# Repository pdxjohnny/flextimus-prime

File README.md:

# Flextimus Prime

Posture monitor

## Getting Started

Make sure you have git configured.

```console
git config --global user.name 'Frist Last'
git config --global user.email 'first.last@example.com'
```

Install the git commit hooks. This will ensure that you can only commit if the
source compiles successfully.

> **WARNING** This adds `set auto-load safe-path /` to your `~/.gdbinit` which
> is not safe because when you start gdb it will now execute any commands in the
> `.gdbinit` file in the current directory.

```console
./scripts/install.sh
```

Find out what you should work on

```console
git todo
```

> This will be run every time you pull so that see todos added by others.

Create a new branch for your work

```console
git checkout -b describe_my_intended_changes
```

Now connect the board, and start `st-util`. From the the top level of this repo
run `arm-none-eabi-gdb` or `make gdb`.

Start hacking!

### Dependencies

1. [mbed](https://os.mbed.com/docs/v5.6/tools/setup.html)

## Contributing

See [CONTRIBUTING.md](https://github.com/pdxjohnny/flextimus-prime/blob/master/CONTRIBUTING.md)

## Team

- Max (lead)
- Julian
- John
- fouric

> Fall 2017
> Practicum Project

## Description

Your team will be responsible for designing, constructing, and demonstrating a small project as part of the course. The project is intended to both give you some necessary implementation skills and experience as well as serve as a model for your capstone experience. In fact, the capstone evaluation forms and worksheets will be used in evaluating and grading your practicum project.

You will get experience with PCB schematic and layout tools, project documentation and management tools, revision control systems, PCB assembly, and (depending upon your project) microcontroller IDEs.

Equally important, you will create project requirements, test plans, schedules, and documentation as you would for your capstone project (or a project in industry). Requirements Your project can do almost anything but must satisfy the following course requirements:

- Have one or more inputs or sensors
  - e.g. photodiodes, switches, accelerometers, pressure sensor, network data (wired or wireless), etc.

- Have one or more outputs or transducers
  - e.g. LEDs, LCDs, motors, networking (wired or wireless).

- Have one or more processing modules which control some of the outputs based on the inputs
  - e.g. analog filters, microcontrollers, FPGAs, etc.

- Use a two layer PCB that is between 1 and 16 in 2, with no side of the board being less than 1 inch or more than 12 inches.

- Use components that can be hand soldered or easily soldered in a crude reflow oven (no BGAs, uBGAs, LGAs, or components smaller than 0603 packages allowed)

## Grading Criteria

Your project will be evaluated using the capstone evaluation forms found on the capstone web site.

Portions of your practicum are evaluated separately throughout the course as part of the homework assignments.

Other aspects are evaluated as part of your project demonstration (final project presentation, design documentation, communication (e.g. weekly progress reports)). Originality Ideally, you should choose an original project idea or a new implementation of an existing idea. To receive an A on the practicum project you must not use existing work (unless specifically approved in advance by the instructor in writing).

If you choose to implement an existing design or incorporate existing work (including but not limited to schematics, layout, or code), your maximum achievable grade is a B.

However, you must disclose both what you've borrowed and the source.

Use of existing work that is not disclosed will result in a practicum grade of F. Recommendation It's far more important that your project be complete and functioning than complex. It's essential that you complete all aspects of the project from idea generation through requirements definition, design description/modeling, layout, construction, test, debug, and documentation.

It's important that you demonstrate a working project. A simple project designed and implemented completely by the team using the disciplined design process taught in class and demonstrably working will beat out an overly ambitious project that's incomplete, non-functioning, or haphazardly implemented.

Consider this in choosing a project. That's not to suggest you shouldn't be imaginative or ambitious. Everything else being equal, a creative points.

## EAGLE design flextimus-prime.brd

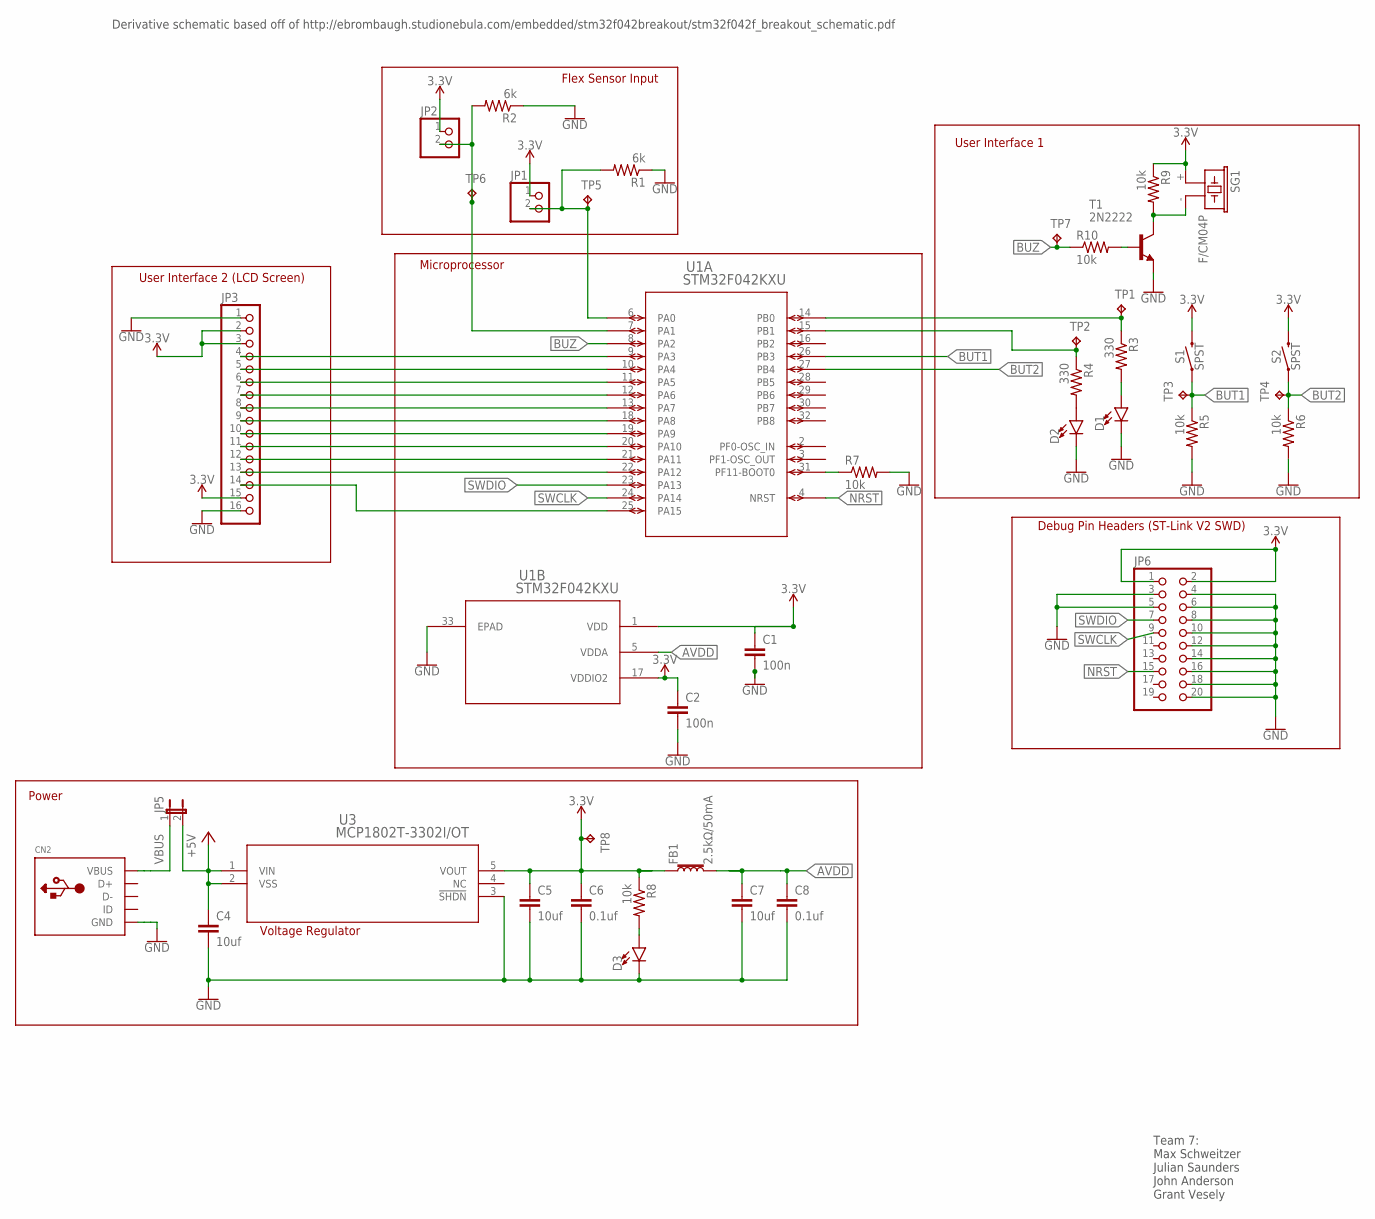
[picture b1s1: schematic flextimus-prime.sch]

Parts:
C1, C2: 100n; C0805
C4, C5, C7: 10uf; C0805
C6, C8: 0.1uf; C0805
CN2: USBMINIB; USB-MINIB
D1, D2, D3: LED10MM; LED_10MM
FB1: 2.5kΩ/50mA; 0603
JP1, JP2: PINHD-1X2; 1X02
JP3: PINHD-1X16; 1X16
JP5: JP1E; JP1
JP6: PINHD-2X10; 2X10
R1, R2: 6k; R0805
R3, R4: 330; R0805
R5, R6, R7, R8, R9, R10: 10k; R0805
S1, S2: SPST; TACTILE_SWITCH_PTH_6.0MM
SG1: F/CM04P
T1: 2N2222; TO92-EBC-OVAL
TP1, TP2, TP3, TP4, TP5, TP6, TP7, TP8: TPB2,54; B2,54
U1: STM32F042KXU; UFQFPN32-5X5MM
U3: MCP1802T-3302I/OT; SOT-23-5_MC

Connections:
3.3V: C1.1, C2.1, C5.1, C6.1, FB1.1, JP1.1, JP2.1, JP3.2, JP3.3, JP3.15, JP6.1, JP6.2, R8.1, R9.1, S1.3 (2), S2.3 (2), SG1.+ (1), TP8.TP, U1.1 (VDD), U1.17 (VDDIO2), U3.5 (VOUT)
+5V: C4.1, JP5.2, U3.1 (VIN), U3.2 (VSS)
AVDD: C7.1, C8.1, FB1.2, U1.5 (VDDA)
BUT1: R5.1, S1.1, TP3.TP, U1.26 (PB3)
BUT2: R6.1, S2.1, TP4.TP, U1.27 (PB4)
BUZ: R10.1, TP7.TP, U1.8 (PA2)
GND: C1.2, C2.2, C4.2, C5.2, C6.2, C7.2, C8.2, CN2.GND, D1.C, D2.C, D3.C, JP3.1, JP3.16, JP6.3, JP6.4, JP6.5, JP6.6, JP6.8, JP6.10, JP6.12, JP6.14, JP6.16, JP6.18, JP6.20, R1.1, R2.1, R5.2, R6.2, R7.2, T1.E, U1.33 (EPAD), U3.3 (!SHDN)
unnamed: JP1.2, R1.2, TP5.TP, U1.6 (PA0)
unnamed: JP2.2, R2.2, TP6.TP, U1.7 (PA1)
unnamed: R3.1, TP1.TP, U1.14 (PB0)
unnamed: JP3.14, U1.25 (PA15)
unnamed: D1.A, R3.2
unnamed: D2.A, R4.2
unnamed: R9.2, SG1.- (2), T1.C
unnamed: R10.2, T1.B
unnamed: D3.A, R8.2
unnamed: JP3.4, U1.9 (PA3)
unnamed: JP3.5, U1.10 (PA4)
unnamed: JP3.6, U1.11 (PA5)
unnamed: JP3.7, U1.12 (PA6)
unnamed: JP3.8, U1.13 (PA7)
unnamed: JP3.9, U1.18 (PA8)
unnamed: JP3.10, U1.19 (PA9)
unnamed: JP3.11, U1.20 (PA10)
unnamed: JP3.12, U1.21 (PA11)
unnamed: JP3.13, U1.22 (PA12)
unnamed: R7.1, U1.31 (PF11-BOOT0)
unnamed: R4.1, TP2.TP, U1.15 (PB1)
NRST: JP6.15, U1.4 (NRST)
SWCLK: JP6.9, U1.24 (PA14)
SWDIO: JP6.7, U1.23 (PA13)
VBUS: CN2.VBUS, JP5.1

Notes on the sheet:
Derivative schematic based off of http://ebrombaugh.studionebula.com/embedded/stm32f042breakout/stm32f042f_breakout_schematic.pdf
Power
User Interface 1
Debug Pin Headers (ST-Link V2 SWD)
Voltage Regulator
Flex Sensor Input
User Interface 2 (LCD Screen)
Microprocessor
Team 7: Max Schweitzer Julian Saunders John Anderson Grant Vesely

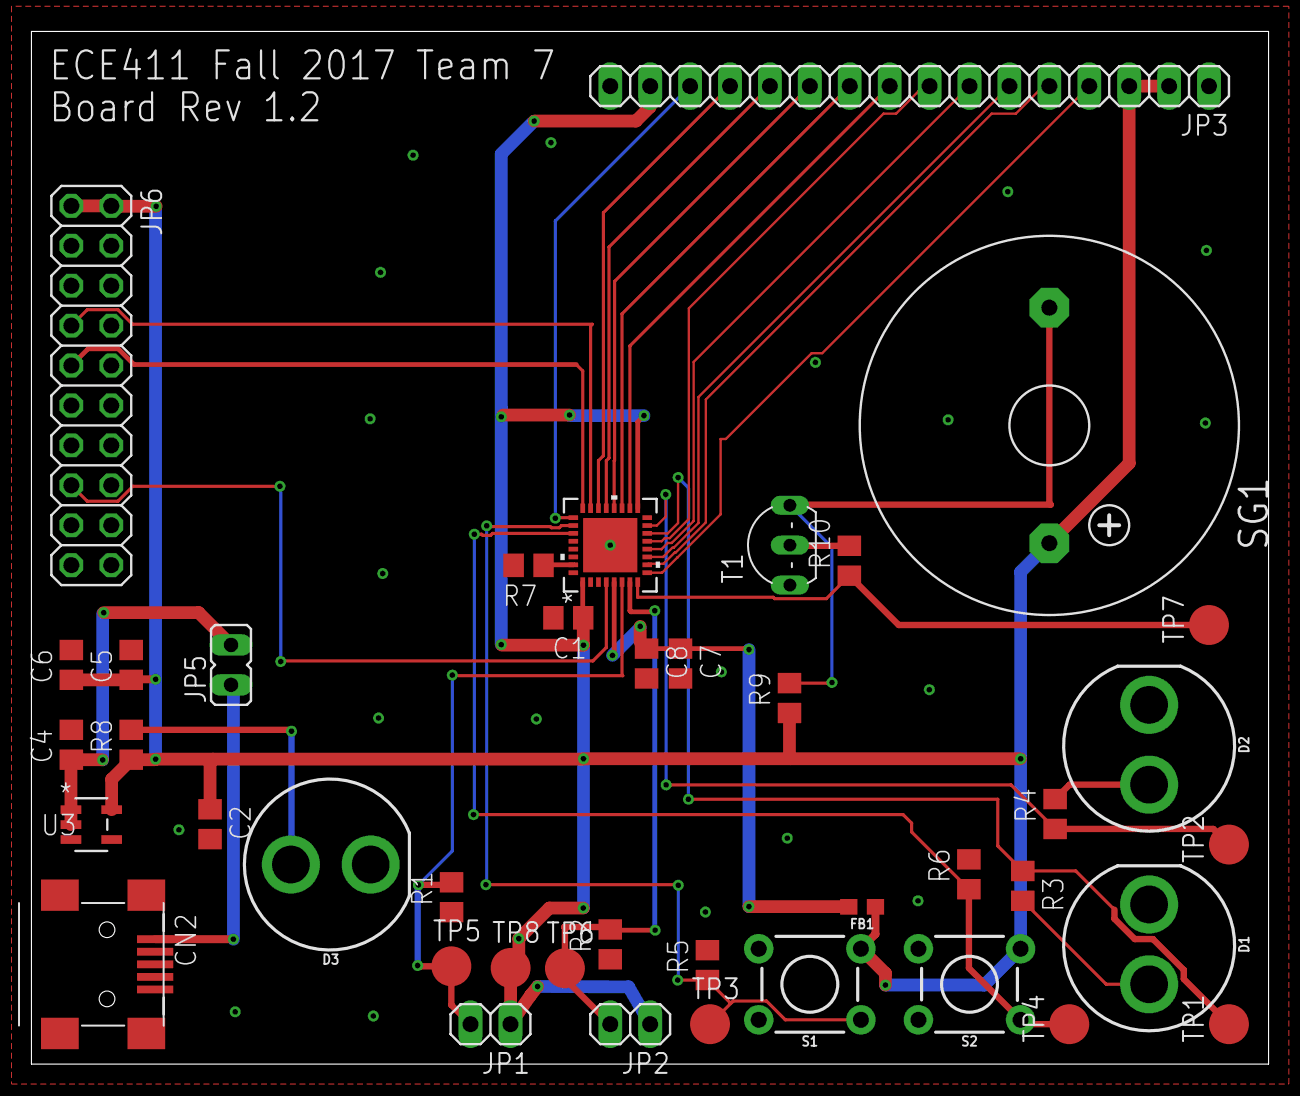
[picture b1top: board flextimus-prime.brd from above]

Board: 2 copper layers, 78.7 x 65.7 mm, 41 parts (0 on the bottom side), 32 nets.

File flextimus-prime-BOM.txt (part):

Partlist exported from C:/Users/Crimson/AppData/Local/Temp/Rar$DIa0.229/flextimus-prime.sch at 11/30/2017 9:41 PM

Part Value             Device                          Package                  Description                                       COPYRIGHT                                                 MANUFACTURER_PART_NUMBER MF MPN OC_FARNELL OC_NEWARK PROD_ID     SF_SKU    TP_SIGNAL_NAME VALUE    VENDOR            
C1   100n              C-EUC0805                       C0805                    CAPACITOR, European symbol                                                                                                                                                                                                       
C2   100n              C-EUC0805                       C0805                    CAPACITOR, European symbol                                                                                                                                                                                                       
C4   10uf              C-EUC0805                       C0805                    CAPACITOR, European symbol                                                                                                                                                                                                       
C5   10uf              C-EUC0805                       C0805                    CAPACITOR, European symbol                                                                                                                                                                                                       
C6   0.1uf             C-EUC0805                       C0805                    CAPACITOR, European symbol                                                                                                                                                                                                       
C7   10uf              C-EUC0805                       C0805                    CAPACITOR, European symbol                                                                                                                                                                                                       
C8   0.1uf             C-EUC0805                       C0805                    CAPACITOR, European symbol                                                                                                                                                                                                       
CN2                    USBMINIB                        USB-MINIB                USB Connectors                                                                                                                                                                                                                   
D1                     LED10MM                         LED_10MM                 LED (Generic)                                                                                                                                                                                                                    
D2                     LED10MM                         LED_10MM                 LED (Generic)                                                                                                                                                                                                                    
D3                     LED10MM                         LED_10MM                 LED (Generic)                                                                                                                                                                                                                    
FB1  2.5kO/50mA        FERRITE_BEAD-0603               0603                     Ferrite Bead (blocks, cores, rings, chokes, etc.)                                                                                                                NDUC-07859                           30O/1.8A                   
JP1                    PINHD-1X2                       1X02                     PIN HEADER                                                                                                                                                                                                                       
JP2                    PINHD-1X2                       1X02                     PIN HEADER                                                                                                                                                                                                                       
JP3                    PINHD-1X16                      1X16                     PIN HEADER                                                                                                                                                                                                                       
JP5                    JP1E                            JP1                      JUMPER                                                                                                                                                                                                                           
JP6                    PINHD-2X10                      2X10                     PIN HEADER                                                                                                                                                                                                                       
R1   6k                R-US_R0805                      R0805                    RESISTOR, American symbol                                                                                                                                                                                                        
R2   6k                R-US_R0805                      R0805                    RESISTOR, American symbol                                                                                                                                                                                                        
R3   330               R-US_R0805                      R0805                    RESISTOR, American symbol                                                                                                                                                                                                        
R4   330               R-US_R0805                      R0805                    RESISTOR, American symbol                                                                                                                                                                                                        
R5   10k               R-US_R0805                      R0805                    RESISTOR, American symbol                                                                                                                                                                                                        
R6   10k               R-US_R0805                      R0805                    RESISTOR, American symbol                                                                                                                                                                                                        
R7   10k               R-US_R0805                      R0805                    RESISTOR, American symbol                                                                                                                                                                                                        
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
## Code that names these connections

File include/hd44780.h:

/******************************************************************************
 * Project        : HAN ESE PRJ2, PRJ1V & PRJ1D
 * File           : HD44780-based LCD implementation
 * Copyright      : 2013 HAN Embedded Systems Engineering
 ******************************************************************************
  Change History:

    Version 1.0 - May 2013
    > Initial revision

******************************************************************************
   Hardware:
                                
                        5V        HD44780-based LCD
                        |        +---------+
            GND|--[10k]-+        |         |
                    |   |  GND|--+ 1 Vss   |
   ------------+    |   +--------+ 2 Vdd   |
               |    +------------+ 3 Vo    |
            PA5+-----------------+ 4 RS    |
            PA6+-----------------+ 5 RW    |
            PA7+-----------------+ 6 E     |
               |              nc-+ 7 DB0   |
               |              nc-+ 8 DB1   |
               |              nc-+ 9 DB2   |
               |              nc-+10 DB3   |
            PA1+-----------------+11 DB4   |
            PA2+-----------------+12 DB5   |
            PA3+-----------------+13 DB6   |
            PA4+-----------------+14 DB7   |
               |     Vdd--[180]--+15 A     |
   ------------+     GND|--------+16 K     |
                                 |         |
                                 +---------+

  http://en.wikipedia.org/wiki/Hitachi_HD44780_LCD_controller

******************************************************************************/
#ifndef _HD44780_H_
#define _HD44780_H_

#include "stm32f0xx.h"
#include "stm32f0xx_gpio.h"
#include "stm32f0xx_rcc.h"
// ----------------------------------------------------------------------------
// Defines
// ----------------------------------------------------------------------------
#define HD44780_GPIO_Port    (GPIOA)

#define HD44780_GPIO_Pin_DB4 (GPIO_Pin_10)  /* PA1: Data bus line 4 */
#define HD44780_GPIO_Pin_DB5 (GPIO_Pin_11)  /* PA2: Data bus line 5 */
#define HD44780_GPIO_Pin_DB6 (GPIO_Pin_12)  /* PA3: Data bus line 6 */
#define HD44780_GPIO_Pin_DB7 (GPIO_Pin_15)  /* PA4: Data bus line 7 */

#define HD44780_GPIO_Pin_RS  (GPIO_Pin_3)  /* PA5: Register Select */
#define HD44780_GPIO_Pin_RW  (GPIO_Pin_4)  /* PA6: Read/Write      */
#define HD44780_GPIO_Pin_E   (GPIO_Pin_5)  /* PA7: Register Select */

// Instruction Register overview
#define HD44780_CLEAR_DISPLAY            ((uint8_t)(0x01))
         
#define HD44780_RETURN_HOME              ((uint8_t)(0x02))
         
#define HD44780_ENTRY_MODE_SET           ((uint8_t)(0x04))
#define HD44780_ENTRY_MODE_SET_ID        ((uint8_t)(0x02))
#define HD44780_ENTRY_MODE_SET_SH        ((uint8_t)(0x01))

#define HD44780_DISPLAY_ONOFF_CONTROL    ((uint8_t)(0x08))
#define HD44780_DISPLAY_ONOFF_CONTROL_D  ((uint8_t)(0x04))
#define HD44780_DISPLAY_ONOFF_CONTROL_C  ((uint8_t)(0x02))
#define HD44780_DISPLAY_ONOFF_CONTROL_B  ((uint8_t)(0x01))

#define HD44780_CURSOR_DISPLAY_SHIFT     ((uint8_t)(0x10))
#define HD44780_CURSOR_DISPLAY_SHIFT_SC  ((uint8_t)(0x08))
#define HD44780_CURSOR_DISPLAY_SHIFT_RL  ((uint8_t)(0x04))

#define HD44780_FUNCTION_SET             ((uint8_t)(0x20))
#define HD44780_FUNCTION_SET_DL          ((uint8_t)(0x10))
#define HD44780_FUNCTION_SET_N           ((uint8_t)(0x08))
#define HD44780_FUNCTION_SET_F           ((uint8_t)(0x04))

#define HD44780_SET_CGRAM_ADDRESS        ((uint8_t)(0x40))

#define HD44780_SET_DDRAM_ADDRESS        ((uint8_t)(0x80))

// Display status bits
#define HD44780_STATUS_BF                (0x0)
#define HD44780_STATUS_AC                (0x1)
#define HD44780_STATUS_BF_AC             (0x2)

// Databus direction
#define HD44780_DATABUS_GPIO_MODE_IN     (GPIO_Mode_IN)
#define HD44780_DATABUS_GPIO_MODE_OUT    (GPIO_Mode_OUT)

// ----------------------------------------------------------------------------
// Function prototypes
// ----------------------------------------------------------------------------
void HD44780_Setup(void);
void HD44780_PowerOn(void);
void HD44780_Clear(void);
void HD44780_Home(void);
void HD44780_GotoXY(uint8_t x, uint8_t y);
void HD44780_WriteInstruction(uint8_t ins, bool checkBusy);
void HD44780_WriteData(uint8_t d, bool checkBusy);
uint8_t HD44780_ReadData(void);
uint8_t HD44780_ReadStatus(uint8_t bf_ac);

// Convenience functions
void HD44780_Putc(uint8_t c);
void HD44780_Puts(uint8_t *str);
uint8_t HD44780_Getc(void);

#endif /* _HD44780_H_ */

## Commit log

2017-10-05 README: Added project description
2017-10-06 ebert: Enabled PEP8 and GNU Complexity
2017-10-06 HACKING: Added HACKING.md
2017-10-11 README: Rename project to PWM and make Max leader
2017-10-11 docs: Redirect to wiki
2017-10-11 README: Redirect to wiki instead of self
    in #7 I accidentally redirected to self instead of the wiki
2017-10-12 spelling pls
2017-10-12 add the fifth horseman
2017-10-12 HACKING: Formatting changes and name change
2017-10-17 Change to something posture
2017-10-26 Name change to Flextimus Prime
2017-10-26 add in-progress preliminary eagle schematic & project
2017-10-26 fix up README to look nicer and reflect the team's actual structure
2017-10-26 ignore EagleCAD temp files (?)
2017-10-26 make preliminary schematic much more interesting
2017-10-26 finished preliminary board BASED OFF OF http://ebrombaugh.studionebula.com/embedded/stm32f042breakout/stm32f042f_breakout_schematic.pdf
2017-11-01 Add final schematic version 1
    Rename to more appropriate name
2017-11-01 Add final schematic version 1 (#30)
    Rename to more appropriate name
2017-11-02 Add project schedule to repo
2017-11-02 Update name
2017-11-02 Fix typo and change name
    Fixes typo that was causing a conflict for tasks
2017-11-02 final schematic?
2017-11-02 actually final schematic
2017-11-02 add bypass capacitor to power supply of MCU
2017-11-06 Remove old file
2017-11-06 CONTRIBUTING.md: Added and referenced in README
2017-11-06 README: Added mbed as dep
2017-11-08 add preliminary bill of materials
2017-11-08 Add two routing options for prelim board layout
2017-11-09 Added UART
2017-11-09 tidy schematic and board files; preliminary layout is a go!
2017-11-09 Add files via upload (#39)
2017-11-09 Formatting and stopped work on USART for now
2017-11-12 .gitignore: Added ctags file
2017-11-13 src: Rewrote using ARM CMSIS libs provided by ST
2017-11-13 Using ARM CMSIS libs provided by ST (#41)
    * .gitignore: Added ctags file
    * src: Rewrote using ARM CMSIS libs provided by ST
2017-11-15 Add new board layout and schematic
    Also add new lcd driver to use later
2017-11-15 README: Added script installation and explination
2017-11-15 adc: Pattern of adc_status returning established
2017-11-15 adc: Lock out further conversions while one is in progress
2017-11-15 adc: Added functions based off exampels
2017-11-15 gdbinit: Loads and runs kernel until error
2017-11-15 main: Added note on adc not yet working
2017-11-15 Im an idiot and was using the drivers wrong, fixing...
2017-11-15 better board
2017-11-16 better board, for real
2017-11-16 schematic + board rev 1.2
2017-11-16 minor tweaks to board rev 1.2
2017-11-16 Auto stash before merge of "master" and "origin/master"
2017-11-16 minor trace tweak
2017-11-16 Add minor fixes for board
    Removes DRC error for overlap
    Increases width of missed power trace
2017-11-19 Add support and test for HD44780 LCD driver
    Needs commenting and clean up, but
    test code works with HD44780
2017-11-19 WIP Code. Needs lots of work.
    Just the basic framework I had laid out the other day. Needs a lot of work and probably doesn't even compile yet.
2017-11-22 Makefile: Find ARM toolchain version dynamicly
2017-11-22 Makefile: Fix dynamicly getting ARM toolchain version
2017-11-23 Updated and added files
    Added the rest of the blinky files for ease of use.
    Updated test.c code which has the basic structure and functions for the code.
    Updated main.c (Edited Blinky main) for simple hardware testing
    I took some of the functions from test.c and put them in main.c just for hardware testing purposes. This main.c is still basically the Blinky main.c but changed. (Though most of what is in the blinky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
2017-11-24 adc: Conversion working
2017-11-24 adc: Started transition to interrupts
2017-11-26 add stencil file
2017-11-27 adc: Random things almost have interrupts working
2017-11-27 adc: Added some ADC watchdog code
    For some reason this is jumping to the Default handler. Last commit it
    correctlyl goes to the adc_handler. This needs to be fixed.
2017-11-28 Revert "WIP: adc code"
2017-11-29 adc: Interrupt are not quite working, sometims working sometimes not, propably and ordering issue
2017-11-29 Fix LCD 2 row mode
    Fixes a missed set up instruction
2017-11-29 adc: adc_handler was triggered
2017-11-30 scripts: install.sh now makes gdb unsafe
2017-11-30 README: Added gdb instructions
2017-11-30 Makefile: Added gdb target
2017-11-30 adc: ADC conversion interrupt working
2017-11-30 adc: Watchdog code primed
2017-11-30 adc: adc_down powers off ADC
2017-11-30 gpio: Documented gpio up, down, and input
2017-11-30 gpio: Button interrupts working
2017-11-30 Tidy up
2017-11-30 gpio: IRQ clearing for EXTI on GPIO
2017-11-30 gpio: Added gpio_asserted_irq
2017-11-30 Button test reading from ADC
2017-11-30 adc: continuous capture
2017-11-30 adc: Continuous conversion fixes
2017-11-30 adc: Start max and min at 2000
2017-11-30 adc: No longer using unknown conversions from examples
2017-11-30 adc: Fixed channel config
2017-11-30 main: flextimus_prime_config_pressed configures ADC watchdog
2017-11-30 adc: awd: Comments
2017-12-01 main: Using continous conversion instead of ADC AWD
2017-12-01 Updated Bill of Materials
2017-12-01 LCD pin headers added
2017-12-01 add test plan
2017-12-02 Redefine flex sensor GPIO
2017-12-02 Fix ADC priority
2017-12-02 util: Fixed using c++ syntax
2017-12-02 adc: Timeout uses correct c instead of c++
2017-12-02 Old Gpio Init
2017-12-02 Added include/stm32f042.h
2017-12-02 gpio: Using ODR
2017-12-02 main: starting conversions on adrdy
2017-12-02 main: Only buzz if we have been configured once before
2017-12-02 Removed Flex sensor old init
2017-12-02 main: Its all in the loop
2017-12-02 Delay for buzzer
    Testing a delay
2017-12-02 Add a check to turn the fucking buzzer off
2017-12-03 gpio: Added button debouncing
2017-12-03 main: Config LED as buzzer
2017-12-03 main: Polling loop works!
2017-12-03 main: Using buzzer
2017-12-05 It fucking works.
2017-12-05 Use a quick delay hack.
    Temporary, hopefully we find a work around for this.
2017-12-05 Messages work, most everything works.
    TODO: Make it so bad posture message doesn't constantly write
2017-12-05 Everything works!
2017-12-06 Last commit, fix two small bugs
    Button debounce delay increased, and now we don't beep unless you've been configured at least once.
2017-12-06 Actual final
2017-12-06 more tidy up?

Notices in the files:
parts and their libraries:
SparkFun-LED: Licensing: Creative Commons ShareAlike 4.0 International - https://creativecommons.org/licenses/by-sa/4.0
COPYRIGHT: Copyright C 2016 Accelerated Designs. All rights reserved
